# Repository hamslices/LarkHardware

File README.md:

# Lark - Thermal Print Engine Controller

**Version:** 01.00.01  
**Author:** HamSlices  
**License:** CERN Open Hardware Licence v2 - Strongly Reciprocal  

## This Design Still Needs Bench Tested, WIP, waiting on boards (10/27/2025)

This repository contains the complete hardware design files for the Lark, a controller board specifically designed for the **FUJITSU FTP-68EMCL112-R** 8-inch thermal print mechanism.

The goal of this project is to provide a fully open-source hardware solution for driving this excellent thermal printer, suitable for custom projects, prototyping, or integration into larger systems.

## Repository Contents

This repository includes all the necessary resources to build and case the hardware:

*   **Lark Controller Board**: The core of the project, designed to drive the Fujitsu thermal printer.
*   **Front I/O Board**: A separate PCB for user-facing controls and connectors.
*   **STLink-V2 Adapter**: A small adapter PCB to easily connect an STLink-V2 for programming and debugging.
*   **3D Printable Enclosures**: Includes custom cases for the Lark board, the Front I/O board, and a test enclosure for the print mechanism itself.

## Directory Structure

Here is a breakdown of the repository's structure:

*   **`/3D`**: Contains 3D models of the various hardware components and enclosures.
*   **`/CubeMX_Lark`**: The STM32CubeMX project file (`.ioc`) for configuring the Lark's microcontroller.
*   **`/Demo Case`**: Files for the 3D printable enclosures for the Lark board, Front I/O, and the print mechanism.
*   **`/img`**: Images, screenshots, and logos related to the project.
*   **`/Kicad Project Files`**: The source files for all hardware designed in KiCad.
    *   **`/FrontIO`**: KiCad project for the Front I/O board.
    *   **`/Lark`**: KiCad project for the main Lark controller board.
    *   **`/STLink_adapter`**: KiCad project for the STLink-V2 adapter.
*   **`/lib`**: Custom KiCad schematic symbols and PCB footprints created for this project.
*   **`/Production_Files`**: Ready-to-manufacture files (Gerbers and BOMs) for all PCBs.

## Getting Started

To work with the hardware design files, you will need to install the latest version of [KiCad](https://www.kicad.org/).

The 3D models are provided in STEP format and can be viewed with any compatible software.

The production files located in the `/Production_Files` directory are ready to be sent to a PCB manufacturer for fabrication and assembly.

## Software / Firmware

The firmware and software for the Lark controller is licensed under the **GPL v3** and is maintained in a separate repository.

## License

The hardware design files in this repository (schematics, PCB layouts, 3D models, etc.) are licensed under the **CERN Open Hardware Licence v2 - Strongly Reciprocal (CERN-OHL-S)**.

A full copy of the license is available in the `LICENSE` file in this repository. In essence, this license allows you to use, study, modify, and share the hardware designs, provided that you share any modifications or derivative works under the same license.

---
*Lark Print Engine © HamSlices 2025*

[The Lark Project](https://github.com/hamslices/The-Lark-Project)

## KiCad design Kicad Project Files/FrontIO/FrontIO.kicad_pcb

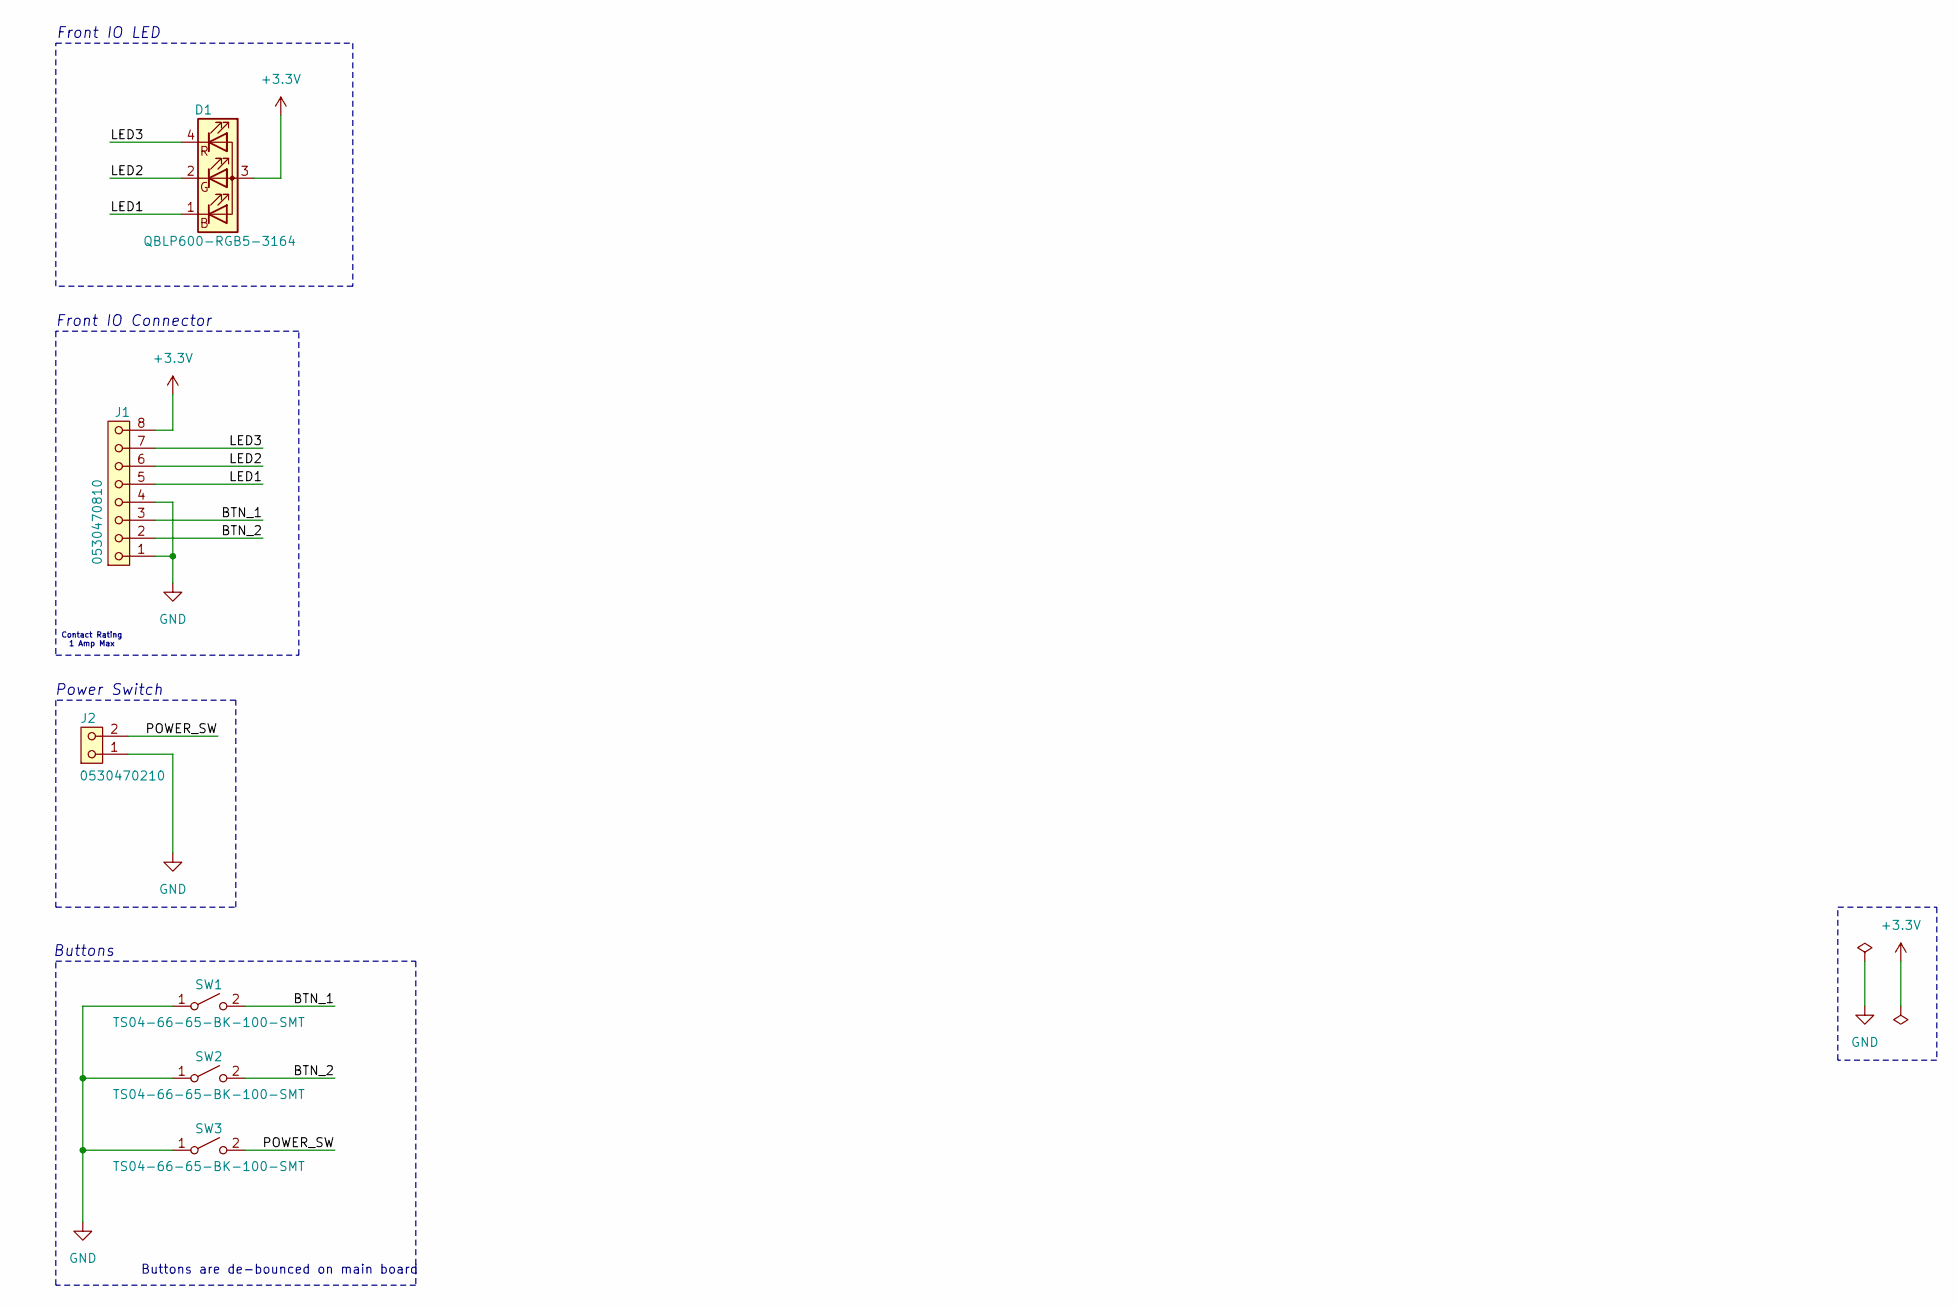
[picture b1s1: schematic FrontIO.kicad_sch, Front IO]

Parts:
D1: QBLP600-RGB5-3164; MPN QBLP600-RGB5-3164
J1: 0530470810; MPN 0530470810
J2: 0530470210; 530470210; MPN 0530470210
SW1, SW2, SW3: TS04-66-65-BK-100-SMT; MPN TS04-66-65-BK-100-SMT

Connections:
+3.3V: D1.3 (A), J1.8
/BTN_1: J1.3, SW1.2 (B), SW1.4 (B)
/BTN_2: J1.2, SW2.2 (B), SW2.4 (B)
/LED1: D1.1 (BK), J1.5
/LED2: D1.2 (GK), J1.6
/LED3: D1.4 (RK), J1.7
/POWER_SW: J2.2, SW3.2 (B), SW3.4 (B)
GND: J1.1, J1.4, J2.1, SW1.1 (A), SW1.3 (A), SW2.1 (A), SW2.3 (A), SW3.1 (A), SW3.3 (A)

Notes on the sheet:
Buttons are de-bounced on main board
Power Switch
Contact Rating 1 Amp Max
Buttons
Front IO Connector
Front IO LED

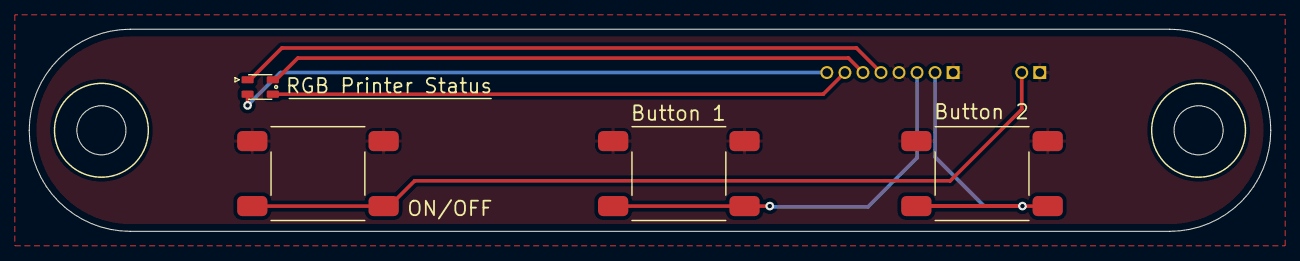
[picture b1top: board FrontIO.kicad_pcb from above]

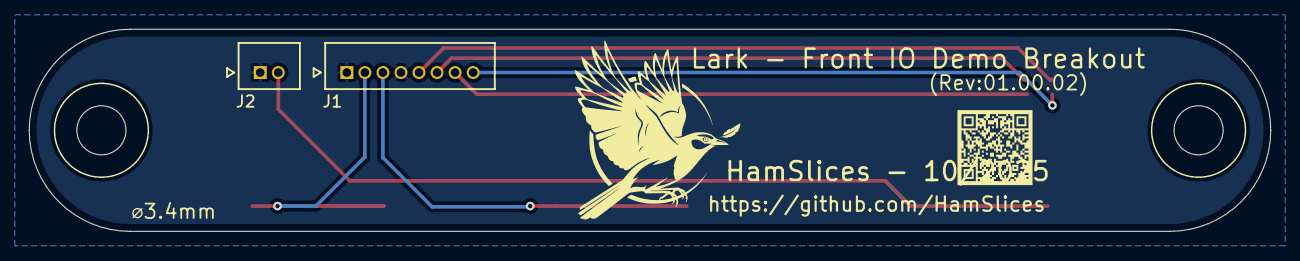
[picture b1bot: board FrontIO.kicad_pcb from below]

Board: 2 copper layers, 86.0 x 14.0 mm, 6 parts (2 on the bottom side), 8 nets.

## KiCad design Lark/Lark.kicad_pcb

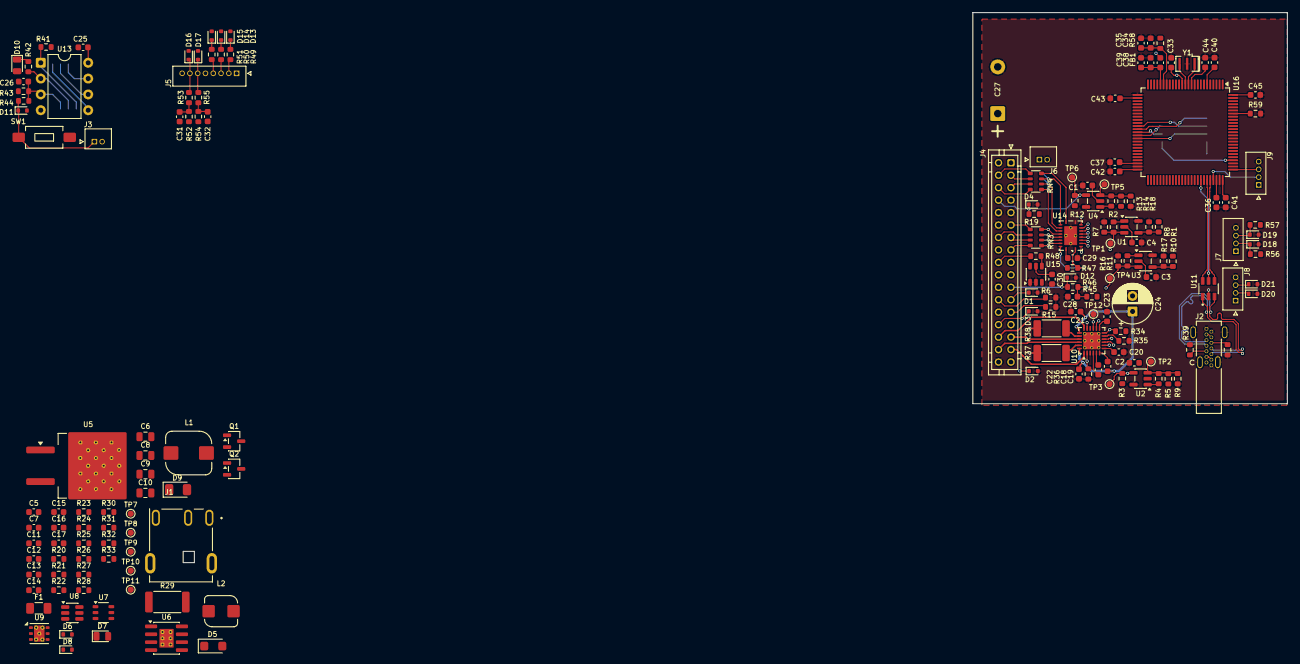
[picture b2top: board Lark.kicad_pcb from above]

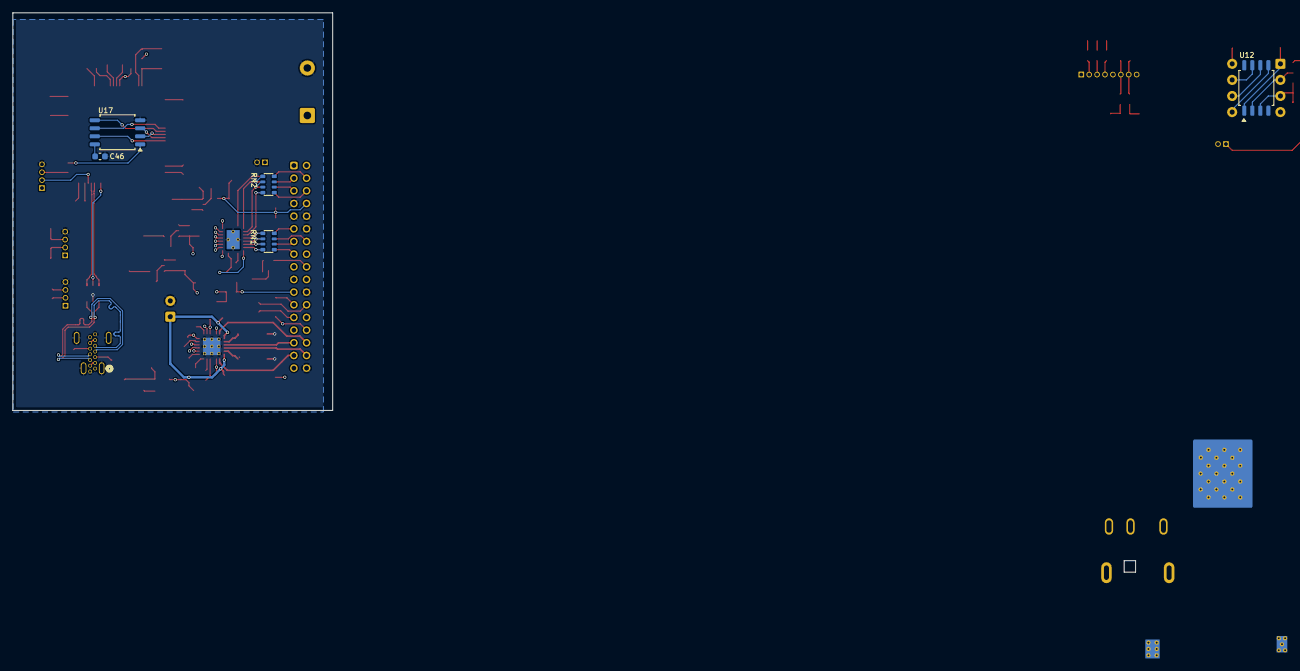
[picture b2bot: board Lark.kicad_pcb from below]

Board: 6 copper layers, 176 parts (5 on the bottom side), 118 nets.

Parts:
C1, C2, C3, C4, C7, C12, C13, C18, C19, C21, C22, C23, C25, C26, C28, C29, C30, C31, C32, C33, C35, C39, C40, C41, C42, C43, C44, C45, C46: 0.1µF; C_0603
C5: 18pF; C_0603
C6, C8, C9, C10: 22µF; C2012X5R1V226M125AC
C11: 6800pF; C_0603
C14: 4.7µF; C_0603
C15, C16: 10µF; C_0603
C17: 22µF; C_0603
C20: 0.22µF; C_0603
C24: 100µF; ECA-1VM101
C27: 6800µF; EEU-HD1V682_Right-Angle
C34, C38: 1µF; C_0603
C36, C37: 2.2µF; C_0603
D1, D2, D3, D4, D11, D12, D13, D14, D15, D16, D17, D18, D19, D20, D21: ESD5Z3.3T1G
D5: SZSMF6L28AT3G
D6, D8: BZT52C15T-7; BZT52C10T-7
D7, D10: LTST-C171GKT; LED_0805
D9: SS26FL
F1: 8A Slow Blow; 3413.0326.22
FB1: 220 Ohms; MPZ1608S221ATA00
J1: 54-00128
J2: 2169890002; CONN_2169890002_MOL
J3, J6: 0530470210; 530470210
J4: B34B-PHDSS; JST_PHD_B34B-PHDSS_2x17_P2.00mm_Vertical
J5: 0530470810
J7, J8, J9: 0530470410
L1: 4.7µH; CLF7045NIT-4R7N-D
L2: 15µH; CLF5030NIT-150M-D
Q1, Q2: MMBT2222A-7-F
R1, R7, R10, R16, R23, R33: 15kΩ; R_0603
R2, R5, R11: 220kΩ; R_0603
R3, R12: 3kΩ; R_0603
R4, R13, R24: 100kΩ; R_0603
R6, R15, R30, R50, R51: 100Ω; R_0603
R8, R17: 24kΩ; R_0603
R9: 365kΩ; R_0603
R14, R31: 51kΩ; R_0603
R18: 178kΩ; R_0603
R19, R58: 0R; R_0603
R20: 402kΩ; R_0603
R21, R26, R28, R34, R35, R41, R43, R45, R47, R52, R54, R59: 10KΩ; R_0603
R22: 20KΩ; R_0603
R25, R32, R42, R44, R46, R53, R55: 1KΩ; R_0603
R27, R36: 100KΩ; R_0603
R29: 220Ω; R_2512
R37, R38: 400mΩ; R_2010
R39, R40: 5.1KΩ; R_0603
R48: 33Ω; R_0603
R49: 280Ω; R_0603
R56, R57: 4.7KΩ; R_0603
RN1, RN2: 10kΩ; RAVF_164D
RN3, RN4: 33Ω; RAVF_164D
SW1: PTS636 SP50 SMTR LFS
TP1, TP2, TP3, TP4, TP5, TP6, TP7, TP8, TP9, TP10, TP11, TP12: TestPoint; TestPoint_Pad_D1.0mm
U1, U2, U3, U4: MIC7211YM5-TR; SOT-23-5
U5: SQM120P06-07L_GE3
U6: BD9E302EFJ-E2
U7: SI3474DV-T1-BE3
U8: BD9G102G-LBTR
U9: LD39200PU33R
U10: A4985SESTR-T; QFN-24-1EP_4x4mm_P0.5mm_EP2.75x2.75mm_ThermalVias
U11: USBLC6-2SC6; SOT95P280X145-6N
U12: ATTINY85-20SU; 8-SOIC_5.3x8.2
U13: ATTINY85-20PU; DIP-8_W7.62mm
U14: SN74LVC541ARGYR
U15: SN74LVC2G34DBVR; SOT-23-6
U16: STM32H743VIT6
U17: W25Q128JVSIQ
Y1: 8Mhz; CSTNE8M00G550000R0

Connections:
+3.3V: C1.2, C2.2, C3.2, C4.2, C16.1, C23.1, C29.1, C30.1, C40.1, C41.1, C42.1, C43.1, C44.1, C45.1, C46.2, FB1.1, J4.16, J4.26, J4.27, J5.1, J7.1, J8.1, J9.1, R1.1, R3.1, R5.1, R10.1, R12.1, R14.1, R34.1, R45.1, R47.1, R52.1, R54.1, R56.1, R57.1, R58.1, RN1.5 (R4.2), RN1.6 (R3.2), RN1.7 (R2.2), RN1.8 (R1.2), RN2.5 (R4.2), RN2.6 (R3.2), RN2.7 (R2.2), RN2.8 (R1.2), TP7.1, U1.2 (V+), U2.2 (V+), U3.2 (V+), U4.2 (V+), U9.1 (OUT), U9.2 (SENSE), U10.13 (VDD), U14.20 (VCC), U15.5 (VCC), U16.6 (VBAT), U16.11 (VDD), U16.27 (VDD), U16.50 (VDD), U16.75 (VDD), U16.100 (VDD), U17.8 (VCC)
+3.3VBC: C17.1, C25.1, D10.2 (A), L2.2, R31.1, R41.1, R43.1, TP8.1, U12.8 (VCC), U13.8 (VCC)
+4V: C5.2, C9.1, C10.1, C15.1, L1.1, R20.1, TP9.1, U9.5 (EN), U9.6 (IN)
+5V: J2.A4 (VBUS), J2.A9 (VBUS), J2.B4 (VBUS), J2.B9 (VBUS), U11.5, U16.68 (PA9)
+24V: C7.2, C8.1, C19.1, C21.1, C22.1, C24.1, C27.1, D7.2 (A), J4.1, J4.2, J4.19, J4.20, J6.1, R29.1, TP11.1, U5.2 (D), U6.2 (VIN), U6.3 (EN), U10.19 (VBB1), U10.24 (VBB2)
+24VBC: C6.1, C14.1, D5.1 (Cathode), D6.1 (K), F1.2, R21.1, R28.1, TP10.1, U5.3 (S), U8.4 (EN), U8.5 (VCC)
/Auxiliary/GPIOA: D20.1 (Cathode), J8.2
/Auxiliary/GPIOB: D21.1 (Cathode), J8.3
/Auxiliary/SCL: D19.1 (Cathode), J7.3, R57.2, U16.92 (PB6)
/Auxiliary/SDA: D18.1 (Cathode), J7.2, R56.2, U16.93 (PB7)
/Boot Controller/IO3: R42.2, U12.2 (PB3), U13.2 (PB3)
/Boot Controller/IO4: C26.1, R43.2, R44.2, U12.3 (PB4), U13.3 (PB4)
/Boot Controller/MCURST: R41.2, U12.1 (PB5), U13.1 (PB5)
/Boot Controller/POWER_SW: D11.1 (Cathode), J3.1, R44.1, SW1.2 (B)
/FTP-68EMCL Connector/Buffers/Y1: RN1.4 (R4.1), RN3.1 (R1.1), U14.18 (Y1)
/FTP-68EMCL Connector/Buffers/Y2: RN1.3 (R3.1), RN3.2 (R2.1), U14.17 (Y2)
/FTP-68EMCL Connector/Buffers/Y3: RN1.2 (R2.1), RN3.3 (R3.1), U14.16 (Y3)
/FTP-68EMCL Connector/Buffers/Y4: RN1.1 (R1.1), RN3.4 (R4.1), U14.15 (Y4)
/FTP-68EMCL Connector/Buffers/Y5: RN2.4 (R4.1), RN4.1 (R1.1), U14.14 (Y5)
/FTP-68EMCL Connector/Buffers/Y6: RN2.2 (R2.1), RN4.2 (R2.1), U14.13 (Y6)
/FTP-68EMCL Connector/Buffers/Y7: RN2.1 (R1.1), RN4.3 (R3.1), U14.12 (Y7)
/FTP-68EMCL Connector/Buffers/Y8: RN4.4 (R4.1), U14.11 (Y8)
/FTP-68EMCL Connector/Buffers/Y9: R48.2, U15.4 (Y2)
/FTP-68EMCL Connector/CLK: U14.2 (A1), U16.29 (PA5)
/FTP-68EMCL Connector/CLOCK: J4.15, RN3.8 (R1.2)
/FTP-68EMCL Connector/DATA: J4.4, RN4.5 (R4.2)
/FTP-68EMCL Connector/DIN: U14.9 (A8), U16.31 (PA7)
/FTP-68EMCL Connector/HUP: C28.1, R45.2, R46.1
/FTP-68EMCL Connector/MTA: J4.32, U10.22 (OUT2A)
/FTP-68EMCL Connector/MTB: J4.29, U10.21 (OUT1A)
/FTP-68EMCL Connector/MT/A: J4.31, U10.1 (OUT2B)
/FTP-68EMCL Connector/MT/B: J4.30, U10.18 (OUT1B)
/FTP-68EMCL Connector/PHK_M: J4.24, R6.1
/FTP-68EMCL Connector/PHK_P: J4.25, R15.1
/FTP-68EMCL Connector/SW1: D12.1 (Cathode), J4.21, R46.2
/FTP-68EMCL Connector//LATCH: J4.18, R48.1
/FTP-68EMCL Connector//OE: R47.2, U14.1 (/OE1), U14.19 (/OE2)
/FTP-68EMCL Connector//STROBE_1: J4.13, RN3.7 (R2.2)
/FTP-68EMCL Connector//STROBE_2: J4.14, RN3.6 (R3.2)
/FTP-68EMCL Connector//STROBE_3: J4.11, RN3.5 (R4.2)
/FTP-68EMCL Connector//STROBE_4: J4.5, RN4.7 (R2.2)
/FTP-68EMCL Connector//STROBE_5: J4.6, RN4.8 (R1.2)
/FTP-68EMCL Connector//STROBE_6: J4.3, RN4.6 (R3.2)
/FrontIO/BTN1: C32.1, R54.2, R55.1
/FrontIO/BTN2: C31.1, R52.2, R53.1
/FrontIO/BTN_1: D17.1 (Cathode), J5.6, R55.2
/FrontIO/BTN_2: D16.1 (Cathode), J5.7, R53.2
/FrontIO/LED1: J5.4, R51.1
/FrontIO/LED2: J5.3, R50.1
/FrontIO/LED3: J5.2, R49.1
/FrontIO/PWM1: D15.1 (Cathode), R51.2, U16.63 (PC6)
/FrontIO/PWM2: D14.1 (Cathode), R50.2, U16.64 (PC7)
/FrontIO/PWM3: D13.1 (Cathode), R49.2, U16.65 (PC8)
/MCU/ADC_CH1: R19.1, U16.91 (PB5)
/MCU/BOOT0: R59.1, U12.7 (PB2), U13.7 (PB2), U16.94 (BOOT0)
/MCU/H_TMP: R13.1, U4.1
/MCU/MARK: R2.1, U1.1
/MCU/M_TMP: R4.1, U2.1
/MCU/NRST: C33.1, U12.6 (PB1), U13.6 (PB1), U16.14 (NRST)
/MCU/OSC_IN: U16.12 (PH0), Y1.1
/MCU/OSC_OUT: U16.13 (PH1), Y1.3
/MCU/PAPER: R11.1, U3.1
/MCU/QSPI_CLK: U16.36 (PB2), U17.6 (CLK)
/MCU/QSPI_IO0: U16.37 (PE7), U17.5 (DI/IO_{0})
/MCU/QSPI_IO1: U16.38 (PE8), U17.2 (DO/IO_{1})
/MCU/QSPI_IO2: U16.39 (PE9), U17.3 (~WP/IO_{2})
/MCU/QSPI_IO3: U16.40 (PE10), U17.7 (~HOLD/~RESET/IO_{3})
/MCU/QSPI_NCS: U16.79 (PC11), U17.1 (~CS)
/MCU/SWCLK: J9.3, U16.76 (PA14)
/MCU/SWDIO: J9.2, U16.72 (PA13)
/MCU/VCAP1: C37.1, U16.48 (VCAP)
/MCU/VCAP2: C36.1, U16.73 (VCAP)
/MCU/VDDA: C38.1, C39.1, FB1.2, U16.21 (VDDA)
/MCU/VREF: C34.1, C35.1, R58.2, U16.20 (VREF+)
/MCU//SLEEP: R34.2, U10.12 (/SLEEP)
/Motor Driver/CP1: C18.1, U10.4 (CP1)
/Motor Driver/CP2: C18.2, U10.5 (CP2)
/Motor Driver/ROSC: R35.1, U10.11 (ROSC)
/Motor Driver/SENSE1: R38.1, U10.20 (SENSE1)
/Motor Driver/SENSE2: R37.1, U10.23 (SENSE2)
/Motor Driver/VCP: C19.2, U10.6 (VCP)
/Motor Driver/VREF: TP12.1, U10.15 (REF), U16.28 (PA4)
/Motor Driver/VREG: C20.1, U10.7 (VREG)
/Motor Driver//EN: R36.1, U10.2 (/EN)
/Power/BOOT: C12.1, U6.1 (BOOT)
/Power/COMP: C11.2, U6.6 (COMP)
/Power/FB_1: R31.2, R33.1, U8.3 (FB)
/Power/FB_2: C5.1, R20.2, R24.1, U6.5 (FB)
/Power/PWR_EN: R25.1, R27.1, R32.1, U12.5 (PB0), U13.5 (PB0)
/Power/SW: C12.2, L1.2, U6.8 (SW)
/Sensors/HTMP: D4.1 (Cathode), J4.8, R12.2, R19.2, TP6.1, U4.4 (-)
/Sensors/MTMP: D2.1 (Cathode), J4.33, R3.2, TP3.1, U2.4 (-)
/Sensors/PHE_M: D1.1 (Cathode), J4.23, R2.2, R7.1, TP1.1, U1.3 (+)
/Sensors/PHE_P: D3.1 (Cathode), J4.28, R11.2, R16.1, TP4.1, U3.3 (+)
/USB/CC1: J2.A5 (CC1), R39.1
/USB/CC2: J2.B5 (CC2), R40.1
/USB/D+: U11.4, U16.71 (PA12)
/USB/D-: U11.6, U16.70 (PA11)
/USB/USB_N: J2.A7 (D-), J2.B7 (D-), U11.1
/USB/USB_P: J2.A6 (D+), J2.B6 (D+), U11.3
GND: C1.1, C2.1, C3.1, C4.1, C7.1, C8.2, C9.2, C10.2, C14.2, C15.2, C16.2, C17.2, C20.2, C21.2, C22.2, C23.2, C24.2, C25.2, C26.2, C27.2, C28.2, C29.2, C30.2, C31.2, C32.2, C33.2, C34.2, C35.2, C36.2, C37.2, C38.2, C39.2, C40.2, C41.2, C42.2, C43.2, C44.2, C45.2, C46.1, D1.2 (Anode), D2.2 (Anode), D3.2 (Anode), D4.2 (Anode), D5.2 (Anode), D8.2 (A), D9.2 (A), D11.2 (Anode), D12.2 (Anode), D13.2 (Anode), D14.2 (Anode), D15.2 (Anode), D16.2 (Anode), D17.2 (Anode), D18.2 (Anode), D19.2 (Anode), D20.2 (Anode), D21.2 (Anode), J1.2, J1.SH1, J1.SH2, J2.A1 (GND), J2.A12 (GND), J2.B1 (GND), J2.B12 (GND), J2.S1 (SHIELD), J3.2, J4.7, J4.9, J4.10, J4.12, J4.22, J4.34, J5.5, J5.8, J6.2, J7.4, J8.4, J9.4, Q1.2 (E), Q2.2 (E), R6.2, R7.2, R8.2, R9.2, R15.2, R16.2, R17.2, R18.2, R23.2, R24.2, R26.2, R27.2, R33.2, R35.2, R36.2, R37.2, R38.2, R39.2, R40.2, R59.2, SW1.1 (A), U1.5 (V-), U2.5 (V-), U3.5 (V-), U4.5 (V-), U6.4 (AGND), U6.7 (PGND), U6.9 (EP), U7.4 (S), U8.2 (GND), U9.3 (GND), U9.7 (EP), U10.3 (GND1), U10.16 (GND2), U10.25 (EP), U11.2, U12.4 (GND), U13.4 (GND), U14.10 (GND), U14.21 (EP), U15.1 (A1), U15.2 (GND), U16.10 (VSS), U16.19 (VSSA), U16.26 (VSS), U16.49 (VSS), U16.74 (VSS), U16.99 (VSS), U17.4 (GND), Y1.2
unnamed: C11.1, R23.1
unnamed: C6.2, D6.2 (A), R21.2, R22.1, U5.1 (G)
unnamed: D7.1 (K), R26.1
unnamed: D8.1 (K), Q2.3 (C), R28.2, R30.1
unnamed: C13.2, D9.1 (K), L2.1, U8.6 (LX)
unnamed: D10.1 (K), R42.1
unnamed: F1.1, J1.1
unnamed: Q1.1 (B), R25.2
unnamed: Q1.3 (C), R22.2
unnamed: Q2.1 (B), R32.2
unnamed: R1.2, R8.1, U1.4 (-)
unnamed: R4.2, R5.2, R9.1, TP2.1, U2.3 (+)
unnamed: R10.2, R17.1, U3.4 (-)
unnamed: R13.2, R14.2, R18.1, TP5.1, U4.3 (+)
unnamed: R29.2, U7.1 (D1), U7.2 (D2), U7.5 (D3), U7.6 (D4)
unnamed: R30.2, U7.3 (G)
unnamed: C13.1, U8.1 (BST)

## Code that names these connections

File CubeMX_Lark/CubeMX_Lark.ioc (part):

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Mcu.Name=STM32H743VITx
Mcu.Package=LQFP100
Mcu.UserName=STM32H743VITx
PA10.GPIOParameters=GPIO_Label
PA10.GPIO_Label=n_RST
PA10.Signal=GPIO_Output
PA11.Mode=Device_Only
PA11.Signal=USB_OTG_FS_DM
PA12.Mode=Device_Only
PA12.Signal=USB_OTG_FS_DP
PA13\ (JTMS/SWDIO).Mode=Serial_Wire
PA13\ (JTMS/SWDIO).Signal=DEBUG_JTMS-SWDIO
PA14\ (JTCK/SWCLK).Mode=Serial_Wire
PA14\ (JTCK/SWCLK).Signal=DEBUG_JTCK-SWCLK
PA3.Signal=ADCx_INP15
PA4.Signal=COMP_DAC11_group
PA5.Mode=TX_Only_Simplex_Unidirect_Master
PA5.Signal=SPI1_SCK
PA7.Mode=TX_Only_Simplex_Unidirect_Master
PA7.Signal=SPI1_MOSI
PA8.GPIOParameters=GPIO_Label
PA8.GPIO_Label=External_GPIO_B
PA8.Signal=GPIO_Output
PA9.Mode=Activate_VBUS
PA9.Signal=USB_OTG_FS_VBUS
PB0.GPIOParameters=GPIO_Label
PB0.GPIO_Label=PAPER
PB0.Signal=GPIO_Input
PB1.GPIOParameters=GPIO_Label
PB1.GPIO_Label=n_OE
PB1.Signal=GPIO_Output
PB10.GPIOParameters=GPIO_Label
PB10.GPIO_Label=n_SLEEP
PB10.Signal=GPIO_Output
PB14.GPIOParameters=GPIO_Label
PB14.GPIO_Label=BTN2
PB14.Signal=GPIO_Input
PB15.GPIOParameters=GPIO_Label
PB15.GPIO_Label=BTN1
PB15.Signal=GPIO_Input
PB2.Mode=Single Bank 2
PB2.Signal=QUADSPI_CLK
PB6.Mode=I2C
PB6.Signal=I2C1_SCL
PB7.Mode=I2C
PB7.Signal=I2C1_SDA
PC11.Mode=Single Bank 2
PC11.Signal=QUADSPI_BK2_NCS
PC4.GPIOParameters=GPIO_Label
PC4.GPIO_Label=n_LAT
PC4.Signal=GPIO_Output
PC5.GPIOParameters=GPIO_Label
PC5.GPIO_Label=HUP
PC5.Signal=GPIO_Input
PC6.Signal=S_TIM8_CH1
PC7.Signal=S_TIM8_CH2
PC8.Signal=S_TIM8_CH3
PC9.GPIOParameters=GPIO_Label
PC9.GPIO_Label=External_GPIO_A
PC9.Signal=GPIO_Output
PD1.GPIOParameters=GPIO_Label
PD1.GPIO_Label=n_EN
PD1.Signal=GPIO_Output
PD10.GPIOParameters=GPIO_Label
PD10.GPIO_Label=n_STB5
PD10.Signal=GPIO_Output
PD11.GPIOParameters=GPIO_Label
PD11.GPIO_Label=n_STB3
PD11.Signal=GPIO_Output
PD12.GPIOParameters=GPIO_Label
PD12.GPIO_Label=n_STB2
PD12.Signal=GPIO_Output
PD13.GPIOParameters=GPIO_Label
PD13.GPIO_Label=n_STB1
PD13.Signal=GPIO_Output
PD3.GPIOParameters=GPIO_Label
PD3.GPIO_Label=M_TMP
PD3.Signal=GPIO_Input
PD5.GPIOParameters=GPIO_Label
PD5.GPIO_Label=MS1
PD5.Signal=GPIO_Output
PD7.GPIOParameters=GPIO_Label
PD7.GPIO_Label=MS2
PD7.Signal=GPIO_Output
PD8.GPIOParameters=GPIO_Label
PD8.GPIO_Label=n_STB6
PD8.Signal=GPIO_Output
PD9.GPIOParameters=GPIO_Label
PD9.GPIO_Label=n_STB4
PD9.Signal=GPIO_Output
PE10.Mode=Single Bank 2
PE10.Signal=QUADSPI_BK2_IO3
PE11.GPIOParameters=GPIO_Label
PE11.GPIO_Label=MARK
PE11.Signal=GPIO_Input
PE12.GPIOParameters=GPIO_Label
PE12.GPIO_Label=H_TMP
PE12.Signal=GPIO_Input
PE14.GPIOParameters=GPIO_Label
PE14.GPIO_Label=DIR
PE14.Signal=GPIO_Output
PE15.GPIOParameters=GPIO_Label
PE15.GPIO_Label=STEP
PE15.Signal=GPIO_Output
PE7.Mode=Single Bank 2
PE7.Signal=QUADSPI_BK2_IO0
PE8.Mode=Single Bank 2
PE8.Signal=QUADSPI_BK2_IO1
PE9.Mode=Single Bank 2
PE9.Signal=QUADSPI_BK2_IO2
PH0-OSC_IN\ (PH0).Mode=HSE-External-Oscillator
PH0-OSC_IN\ (PH0).Signal=RCC_OSC_IN
PH1-OSC_OUT\ (PH1).Mode=HSE-External-Oscillator
PH1-OSC_OUT\ (PH1).Signal=RCC_OSC_OUT
RCC.HSE_VALUE=8000000
RCC.SYSCLKFreq_VALUE=480000000
RCC.SYSCLKSource=RCC_SYSCLKSOURCE_PLLCLK
board=custom

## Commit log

2025-10-09 Project init
    Porting over design from 'Other' Cad software.
2025-10-10 still porting design over from 'other' cad software.
2025-10-10 Added Front pannel IO Sheet
    - added new Molex connector to project lib.
2025-10-11 added power section to schematic
    It needs revised, due to thermal issue. Specifically in regards to my soft start circuit, the mosfet wont be able to handle the power dissipated during a slow turn on.
2025-10-11 update, WIP
    - Reannotated schematic.
    - Added STM32 device.
    - Fixed High-side switch (removed soft-start cap for device safety).
2025-10-11 Updated schematic, WIP
    - Added NOR flash part.
    - Added new CubeMX config file.
    - Reannotated the schematic.
    - Made some more connections to the MCU.
2025-10-12 Update, WIP
    - Added TVS diode to 24v Supply.
    - Fixed bleeder circuit at some point (I think it was this commit)
    - Added Jumper to connect NTC to ADC. (again I think it was this commit)
2025-10-12 End Of Day Commit.
    nothing worth noting, I think I moved a part or two, no major changes.
2025-10-13 updated WIP
    - fixed high-side switch (swapped out pfets)
    - swapped out bleeder fet.
    - changed a few footprints.
    - changed zeners to 15v ones
    - added soft-start cap back in to the high-side switch.
    (today ive mainly been struggling with the inrush current, but I think its solved now)
2025-10-14 started on layout, WIP
    I'm not a fan of how its going, I feel like I might redo it, before I get to far into it. A patchy foundation makes an unstable house.
2025-10-14 Delete Lark.kicad_dru
    dru was empty, so i deleted it.
2025-10-14 updated layout
    got all the control signals routed finally.
2025-10-15 The right side of the board is finalized.
    - Finalized the logic side of the board (right)
    - Will work on the power section next.
2025-10-15 moved divider line down .5mm
2025-10-15 Working on power section.
    I have the stuff blocked out, but I'm not liking the layout.
    - changed diode and inductor footprints, adjusted margins.
2025-10-16 Update Lark.kicad_pcb
    Working on layout WIP.
2025-10-16 Finishing up the layout, WIP
    - Changed USBC footprint silkscreen.
    - Routed Power Section.
    - Switched from 7A to 10A Fuse.
2025-10-17 minor updates
    - changed npn pins to passive.
    - changed rev to match working revision.
    - minor PCB changes.
    - moved TVS diode next to connector.
    - changed barrel jack silkscreen.
    - changed usbc silkscreen.
2025-10-17 Changed revision again...
    - It dawned on me that this is rev 2, so the rev is now 01.00.1.
    - Added thermal relief to the TH pads so I can actually solder the parts.
    - Added more silkscreen to denote the rev, the github link, and ESD sensitivity of the device.
    - Made minor pcb changes, I moved a test point, and cleaned up some traces.
2025-10-18 Working on bottom silkscreen, WIP
    Finalizing the bottom silkscreen.
2025-10-18 Created Front IO Breakout.
    - Needed for testing and diagnostics.
2025-10-18 Created STLink Adapter PCB
    - changed silk on FrontIO PCB a little.
2025-10-19 backup, WIP.
    - So far i think i have everything the way i want it. I'm going to take another few days to look over everything before i finalize the PCB's
2025-10-19 changed dir structure
2025-10-19 created a demo case for bench testing.
    - The goal is to protect the hardware during testing, to do that, I created a simple case.
2025-10-20 changed dir structure.
2025-10-20 Added Notes
    - Changed AUX power to FAN power, added note about fan.
    - Changed bottom and top silk.
    - Added 24v pour to the top of connector j4, the mid 24v pins remain the same.
2025-10-20 Update Demo Case.zip
    - Updated case design.
    - Added more fillets.
    - At some point I added a honey comb pattern, can't remember when.
    - Files in zip are "FAB Ready". Again this is a demo case, the OEM board should be placed in a propper housing when in use.
2025-10-22 Created a housing for the mech unit.
    I need something to mount to mech unit to. It should be cheap to 3D print, at some point I will place an order for one. Note, this is no an injection molded part, it was designed to be resin printed.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
2025-10-22 Created Release packages for JLCPCB
2025-10-22 Added gerbers + bill of materials
    - Changed connector symbol to include MPN.
    - Added DNP field to lark BOM
2025-10-22 updated git ignore
    - added the schematic QR code to image folder for reference.
2025-10-22 added cad renders from fusion360.
    - I decided to render the assemblies for visual reference.
    - I also included a few exploded assembly views for reference.
    - Used AI to add a cute little Lark to the Mech Assy, I'm calling it the money shot, because it looks golden.
2025-10-22 added readme and lic to project.
2025-10-22 updated gitignore
2025-10-22 Update .gitignore
    - removed redundant entries.
2025-10-22 Added References Docs
    - Added component app notes.
    - Added white papers.
    - Added calculator and other apps source code (relevant to hardware).
    - Added Wiring diagram for the mech connector.
    - Added various Lark project logos (AI generated).
    - Added NON-NDA mech datasheet.
2025-10-22 added schematic pdfs to production files sub directories
    - Added PDF schematics to the production files directory
    - Did not include part placement files, as I am hand assembling the PCB's. However you should be able to generate them from kicad manually with the supplied project files.
2025-10-22 added pcb render
2025-10-23 fixed strobe timing image in schematic, now active low, as it should be
2025-10-23 Update DSView-251023-170413.png
    inverted image for better visibility in the schematic.
2025-10-24 updated PCB image.
2025-10-25 fixed issue with ADC, Rev-ed board.
    Turns out, you can in fact set PB5 to analog, but its use is with I2C1_SMBA, not the ADC, So I changed it to pin PA3. This renders the head temp functionality on revision 01.00.1 null.
2025-10-25 Update CubeMX_Lark.ioc
    changed ioc, it should now have the correct pinout for REV 01.00.02.
2025-10-26 moved logos to another repo.
    - removed all logos from repo.
2025-10-26 added rev 01.00.02 gerbers to repo.
2025-10-27 updated readme.
    - added caution statement about design.
2025-10-29 updated broken QR on Front IO PCB and SCH.
2025-10-29 updated broken QR code in adapter SCH
    - the site i used to gen the QR codes was a subscription site that generated tiny urls. My trial ran out so now all my QR codes are broken.
2025-10-29 Replaced all broken QR coded in SCH and PCB
    - See previous commit for a detailed explanation of the QR code oversight.
